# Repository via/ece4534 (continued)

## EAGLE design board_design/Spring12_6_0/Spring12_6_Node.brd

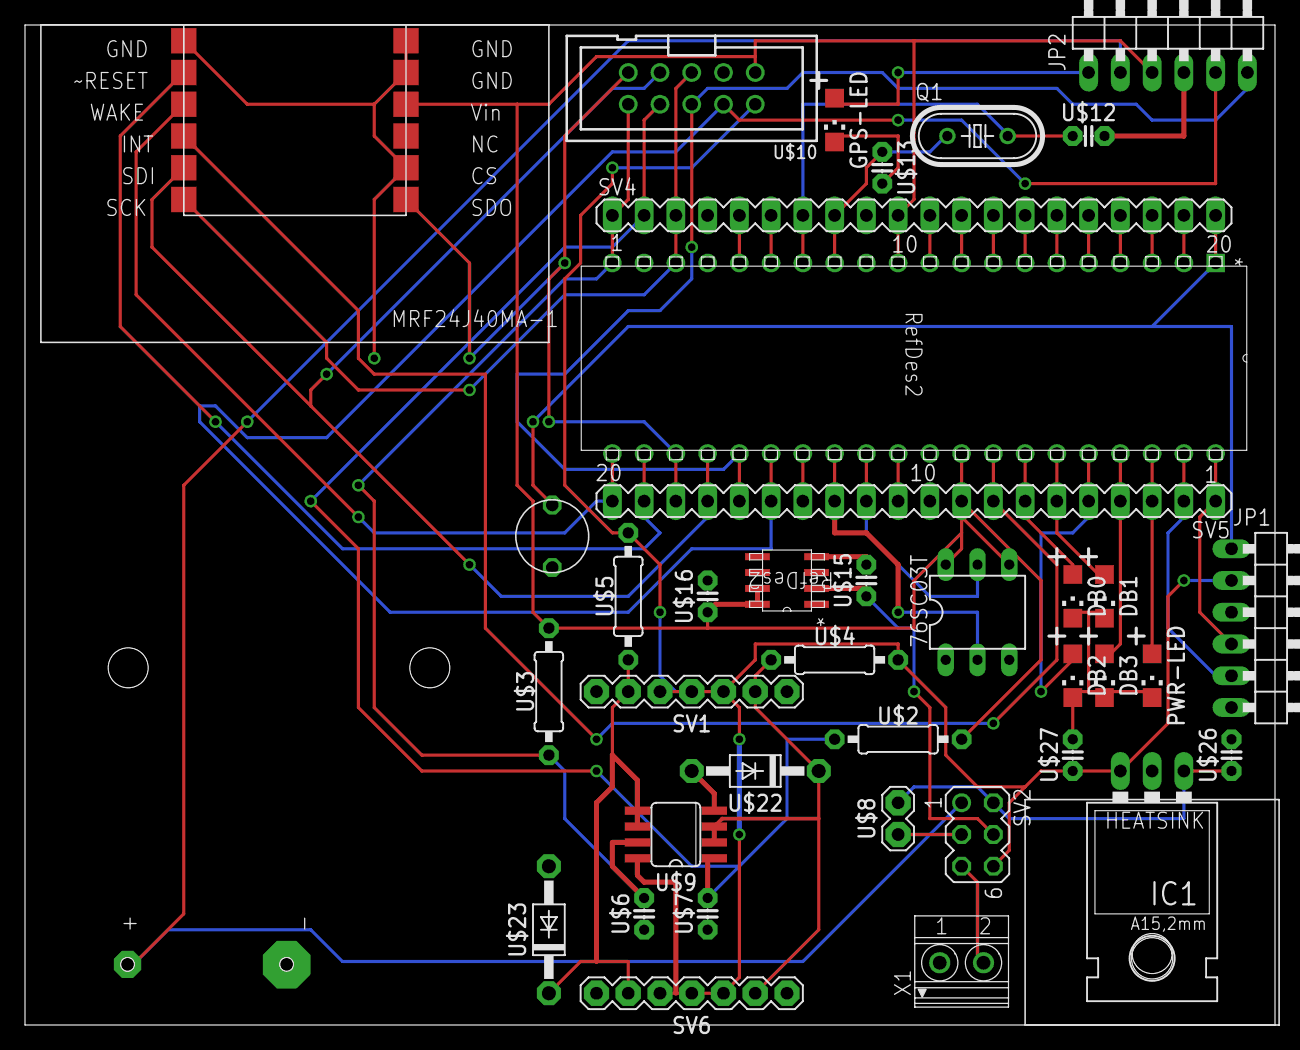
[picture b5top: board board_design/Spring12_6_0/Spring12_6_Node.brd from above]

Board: 2 copper layers, 100.0 x 80.0 mm, 40 parts (0 on the bottom side), 46 nets.

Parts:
76SC03T: I2C Select; DIL06
DB0, DB1, DB2, DB3: LED-SMD-1206; LED1206
GPS-LED: LED-SMD-1206; LED1206
IC1: L78S05CV; 78XXL
JP1: PICKIT; 1X06/90
JP2: GPSR; 1X06/90
PWR-LED: LED-SMD-1206; LED1206
Q1: 20MHz; HC49U-V
SV1, SV6: I2C BUS; MA07-1
SV2: PWR CNTL; MA03-2
SV4, SV5: MA20-1
U$1: PIC18F45J10-X/P; PDIP40_600MC
U$2, U$3: 1k; R-1/4W
U$4, U$5: 330; R-1/4W
U$6, U$7: 100pF; C2.5-5
U$8: CURRENT; MA02-1
U$9: PCA9600SO8; SO08
U$10: DEBUG; 2510-6002
U$11: MRF24J40MA; PCB12
U$12, U$13: 18pF; C2.5-5
U$14: MCP1725-XXXXX/SN; SOIC8-N_MC
U$15, U$16: 10uF; C2.5-5
U$17: 2479-BATTERY
U$22, U$23: 1N5817P; 1N5817
U$25: EVQ-11U05R
U$26: 0.33uF; C2.5-5
U$27: 0.1uF; C2.5-5
U$28: 7-361-BA
X1: 1751248

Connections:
3V3: 76SC03T.4, 76SC03T.6, JP2.3, SV4.10, SV5.9, U$1.11, U$1.32, U$2.2, U$3.2, U$10.1, U$11.10, U$14.7, U$14.8, U$16.1
3V3-REG: SV2.4, U$14.1, U$14.2, U$14.3, U$15.1
5V: IC1.OUT, JP1.2, SV1.3, SV1.4, SV1.5, SV2.6, SV6.3, SV6.4, SV6.5, U$4.2, U$5.2, U$9.8, U$10.2, U$27.1
BATTERY: JP2.2, SV2.1, U$17.P$2
CURRENT: SV2.3, U$8.1
DB-LED0: DB0.A, SV5.7, U$1.34
DB-LED1: DB1.A, SV5.6, U$1.35
DB-LED2: DB2.A, SV5.5, U$1.36
DB-LED3: DB3.A, SV5.4, U$1.37
EXTERNAL: SV2.5, X1.2
GPS-LED: GPS-LED.A, JP2.1
I2C-ADDR0: 76SC03T.2, SV5.13, U$1.28
I2C-ADDR1: 76SC03T.5, SV5.12, U$1.29
I2C-ADDR2: SV5.11, U$1.30
MRF-INT: SV5.8, U$1.33, U$11.4
MRF-RESET: SV5.19, U$1.22, U$11.2
MRF-WAKE: SV5.20, U$1.21, U$11.3
unnamed: SV4.13, U$1.8
unnamed: SV4.6, U$1.15
unnamed: SV4.5, U$1.16
unnamed: SV5.14, U$1.27
unnamed: SV4.19, U$1.2
unnamed: SV4.18, U$1.3
unnamed: SV4.17, U$1.4
unnamed: SV4.16, U$1.5
unnamed: SV4.15, U$1.6
unnamed: SV4.14, U$1.7
unnamed: SV4.12, U$1.9
unnamed: SV4.11, U$1.10
OSC1: Q1.1, SV4.8, U$1.13, U$13.1
OSC2: Q1.2, SV4.7, U$1.14, U$12.1
PGC: JP1.5, SV5.2, U$1.39
PGD: JP1.4, SV5.1, U$1.40
PIC-RESET: JP1.1, SV4.20, U$1.1, U$25.P$1
PWR-LED: PWR-LED.A, SV5.3, U$1.38
REGULATORS: IC1.IN, SV2.2, U$8.2, U$26.1
SCL-BUS: SV1.2, SV6.2, U$4.1, U$9.2, U$9.3, U$22.C
SCL-LOCAL: SV4.2, U$2.1, U$7.2, U$9.1, U$10.8
SDA-BUS: SV1.6, SV6.6, U$5.1, U$9.5, U$9.6, U$23.C
SDA-LOCAL: SV4.1, U$1.20, U$3.1, U$6.2, U$9.7, U$10.10
SPI-MISO: SV5.18, U$1.23, U$10.9, U$11.7
SPI-MOSI: SV5.17, U$1.24, U$10.7, U$11.5
SPI-SCK: SV4.3, U$1.18, U$10.5, U$11.6
UART-RX: JP2.5, SV5.15, U$1.26, U$10.4
UART-TX: JP2.6, SV5.16, U$1.25, U$10.6
VSS: 76SC03T.1, 76SC03T.3, DB0.C, DB1.C, DB2.C, DB3.C, GPS-LED.C, IC1.GND, JP1.3, JP2.4, PWR-LED.C, SV1.1, SV1.7, SV4.9, SV5.10, SV6.1, SV6.7, U$1.12, U$1.31, U$6.1, U$7.1, U$9.4, U$10.3, U$11.1, U$11.8, U$11.11, U$11.12, U$12.2, U$13.2, U$14.4, U$15.2, U$16.2, U$17.P$1, U$22.A, U$23.A, U$25.P$2, U$26.2, U$27.2, X1.1

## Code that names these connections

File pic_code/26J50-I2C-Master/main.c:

/* Compile options:  -ml (Large code model) */
#define I2C_SCL TRISBbits.TRISB4
#define I2C_SDA TRISBbits.TRISB5

#include "maindefs.h"
#include <i2c.h>

void wait_a_little(){
	INTCON &= 0b11111011;
	INTCON |= 0x20;
	TMR0L = 0xFF - 120;
	T0CON = 0b11101000;
	while( ~(INTCON & 0x04) );
	INTCON &= 0b11011011;
}

#define SDAset(n) PORTBbits.RB5=n;LATBbits.LATB5=n
#define SDA PORTBbits.RB5
#define SCLset(n) PORTBbits.RB4=n;LATBbits.LATB4=n
#define SCL PORTBbits.RB4

/*****************************************************/
const char Slave = 0x7C;
const char Comsend = 0x00;
const char Datasend = 0x40;
const char Wake = 0x30;
const char Function = 0x31;
const char Internalosc = 0x14;
const char Powercontrol = 0x56;
const char Followercontrol = 0x6D;
const char Contrast = 0x25;
const char Displayon = 0x0C;
const char Entrymode = 0x06;
const char Clear = 0x01;
const char Line2 = 0xC0;
/*****************************************************/
void I2C_out(unsigned char j)
//I2C Output
{
	WriteI2C1( j );
}
/*****************************************************/
void I2C_Start(void)
{
	StartI2C1();
}
/*****************************************************/
void I2C_Stop(void)
{
	StopI2C1();
}
/*****************************************************/
void Show(unsigned char *text)
{
	int n;
	I2C_Start();
	I2C_out(Slave);
	I2C_out(Datasend);
	for(n=0;n<16;n++){
		I2C_out(*text);
		++text;
	}
	I2C_Stop();
}
/****************************************************
*
Initialization For ST7032i
*
*****************************************************/
void init_LCD()
{
	I2C_Start();
	I2C_out(Slave);
	I2C_out(Comsend);
	I2C_out(0x31);
	I2C_out(Internalosc);
	I2C_out(Contrast);
	I2C_out(Powercontrol);
	I2C_out(Followercontrol);
	I2C_out(Displayon);
	I2C_out(Entrymode);
	I2C_out(Clear);
	I2C_Stop();
}
/*****************************************************/


// This program 
//   (1) prints to the UART and it reads from the UART
//   (2) it "prints" what it reads from the UART to portb (where LEDs are connected)
//   (3) it uses two timers to interrupt at different rates and drive 2 LEDs (on portb)
void main (void)
{
	// ensure the two lines are set for input (we are a slave)
	TRISBbits.TRISB4=0;
	TRISBbits.TRISB5=0;
	//OpenI2C
	SSP1STAT = 0x0; //Slew off
	SSP1CON1 = 0x0;
	SSP1CON2 = 0x0;
	SSP1CON1 |= 0x14;  // enable master
	SSP1ADD = 29;
	SSP1STAT |= SLEW_OFF;	
	IdleI2C1();
	init_LCD();

	while(1)
	{

		Show("ECE4534 is fun!");
	}
}

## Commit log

2012-01-26 Added bibtex file.
2012-01-26 Started latex and integrated mitchd's parts.
2012-01-26 Added wikipedia biblio entries.
2012-01-26 Another IEEE paper.
2012-01-26 Added intro, FS talk, and \x5654's text.
2012-01-28 Skeleton requirements tex.
2012-01-28 Added diagrams.
2012-01-28 Added Jagged's and \x5654's text, added margins.
2012-01-28 Added some stuff about OS, fixed Jagged's equations.
2012-01-28 Updated a pdf.
2012-01-28 Added Dizzeh's section and resized images.
2012-01-29 Added PIC Data
2012-02-01 added overview diagram
2012-02-01 Added some ARM refecences
2012-02-02 Added freertos manual.
2012-02-04 Added some notes on ARM board
2012-02-09 added mobile module block diagram
2012-02-09 Added Jagged's and Dizzeh's images, start of tex.
2012-02-09 Added receiver diagram, added line to Remote module diagram.
2012-02-09 Added second PIC receiver module, integrated Justin's stuff.
2012-02-10 Added calibrate sequence.
2012-02-11 added data polling diagram
2012-02-11 added things
2012-02-11 more stuff
2012-02-11 Combined.
2012-02-12 starting work on 1b
2012-02-13 milestone 1b
2012-02-14 ARM Baseline Code added
2012-02-14 Added code used from milestone 1.
2012-02-14 Move stuff around, haven't attempted build.
2012-02-14 More changes.
2012-02-15 added updated main/i2c
2012-02-17 text file of a few of the tasks to be done
2012-02-17 added my validation/schedule thing
2012-02-17 forgot a bit about the LCD display
2012-02-17 Adding breakdown of work
2012-02-17 Adding unfinished demos thing and modified i2c/LCD ARM code
2012-02-17 Added draft of gantt chart.
2012-02-19 added documentation for the position algorithm
2012-02-19 Adding possibly working calculation task
2012-02-20 added this week's order
2012-02-20 Added initial libfat code.
2012-02-20 fixed up arm code so it actually compiles
2012-02-20 modified main to allow for calculation queue
2012-02-21 made protocol specification
2012-02-25 stuff
2012-02-25 Adding current code, not sure if compiles
2012-02-28 milestone 1b complete
2012-02-29 started working on the board design
2012-02-29 moved and renamed some datasheets
2012-02-29 adding more datasheets
2012-02-29 making progress on the board
2012-03-01 added more datasheets and finished putting all the parts in eagle
2012-03-01 PCB Rev 0 done
2012-03-01 more datasheets?
2012-03-11 working on locatelib
2012-03-11 locatelib initial version
2012-03-12 fixed locatelib header file problems
2012-03-13 added RSSI to dBW conversion
2012-03-15 PCB V2
2012-03-22 fixing up communication between a few arm tasks
2012-03-22 Testing comms between tasks, i2c->calc->lcd
2012-03-22 fixing minor bugs
2012-03-22 derp
2012-03-24 Templates for sdcard read/write should be set up
2012-03-27 set everything up for m4 and beyond maybe, untested
2012-03-27 forgot to throw locate stuff into directory, need to gut .c for m4 and add to project file later
2012-03-27 forgot some files
2012-03-27 changed DMS to DD MM.MMM
2012-03-27 something
2012-03-27 fixed up a bit for milestone 4, still need to gut locatelib and hardcode
2012-03-27 fixing up blatant errors
2012-03-27 more fixes
2012-03-27 test
2012-03-27 removed typedef
2012-03-27 I have to
2012-03-27 too many commits
2012-03-27 this maybe works
2012-03-28 removing object files
2012-03-28 just committing for whenever, need to fix everything
2012-03-29 working stuff
2012-03-29 m4 stuff
2012-03-29 filetask and http modifications for m4 and beyond
2012-03-29 Added source for picdemz board connected to gps.
2012-03-29 Pushed code for MS4 for receiver
2012-03-29 slightly modded stuff
2012-03-29 added matlab code for simulations and such
2012-03-30 ms4 crap
2012-03-30 more simulation junk
2012-04-02 pcb stuff >_>
2012-04-02 Fixed up m4
2012-04-02 streamlining i2ctemp
2012-04-02 removing unnecessary line
2012-04-02 fixed http and filetask a bit
2012-04-02 uh, trying again
2012-04-02 trying again pt. 2
2012-04-05 bitbang crap for LCD x_x
2012-04-09 starting board revision
2012-04-10 adding poster stuff
2012-04-10 pcb part deux
2012-04-12 board design... hopefully done
2012-04-13 set up touchscreen
2012-04-13 minor changes
2012-04-14 more PCB revs
2012-04-16 adding some testcode for touchscreen
2012-04-16 fixing usb
2012-04-17 testing secondary i2c bus
2012-04-18 somewhat working
2012-04-19 Revised tsc code
2012-04-19 slightly revised tsc
2012-04-19 Adding more calibration functionality
2012-04-22 working except minor calibration
2012-04-23 changing back to z only
2012-04-23 Rolling data set up for buffers, message/data handling set up. Need to test both
2012-04-24 changed project requirements document
2012-04-24 added demonstration plan
2012-04-27 comments for 0x5654 and template for untested GPIO things
2012-04-28 testing/fixing file/web stuff
2012-04-28 adding smaller things
2012-04-29 Fixed file/web more, test with GPIO _appears_ to work, template for calc
2012-04-30 added logic analyzer stuff
2012-05-01 various changes from today's CEL session
2012-05-01 asdf
2012-05-01 added files
2012-05-02 stuff from today's GPIO testing
2012-05-03 added LCD datasheet
2012-05-03 pyserial unzipped
2012-05-03 Added 26J50 code.
2012-05-03 Pruned code to remove stuff not being used.
2012-05-03 Implemented I2C request for RSSI values.
2012-05-03 copied matlab code to position_calculator
2012-05-03 et cetera
2012-05-04 jkl;
2012-05-04 Added some really really shitty code to parse nmea strings.
2012-05-04 hurr
2012-05-04 asdasd
2012-05-05 Tweaked things and wrote a test driver. Needs more work.
2012-05-05 Fixed some small problems with the test driver.
2012-05-05 Make it able to output graphs. Note that something still isn't quite right.
2012-05-05 fixed the frequency in test_locatelib.c
2012-05-05 fixed the algorithm structure in test_locatelib
2012-05-05 comments..
2012-05-05 fixed DMS_to_UTM and changed test input to be in this grid
2012-05-05 added distance and bearing calculation to locatelib
2012-05-05 fixed the bearing calculator
2012-05-05 Added checksum verifier to code, and fixed to work with actual nmea strings.
    My first example string was invalid apparently.
2012-05-05 Changed gradient function interface to be simpler.
2012-05-05 Unbroke shit.
2012-05-05 zomg
2012-05-05 Merged in latest PIC code, which afaik is completely functional and tested.
2012-05-05 modified bearing calc
2012-05-06 Added miwi board logic analyzer configuration
2012-05-06 Python buspirate interface
2012-05-06 Finished Python interface and made power measurements
2012-05-06 Pretty graphs of current useage
2012-05-06 Added total current measurements
2012-05-06 shrug
2012-05-06 adding rssi view, fixing dumb case maybe
2012-05-07 Demonstration plan complete
2012-05-08 ms5 stuff
2012-05-08 small tweaks
2012-05-08 adding tasks.tar
2012-05-09 Initial commit for updated sequence diagram stuff.
2012-05-09 Updated sequence diagram.
2012-05-09 Done
